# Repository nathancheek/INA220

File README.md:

# INA220
Lightweight Arduino library for the `INA220` / `INA220-Q1` / `INA219` current sensor

## Introduction
This library is based off [`SV-Zanshin/INA`](https://github.com/SV-Zanshin/INA) but is rearchitected to be much more lightweight.

Each instance of this library class configures all devices with the same settings, and unlike [`SV-Zanshin/INA`](https://github.com/SV-Zanshin/INA) it doesn't rely on EEPROM to store this information. If you need to configure some sensors differently, create a new instance of this class for each unique configuration.

## Breakout Board
An example breakout board is available under [`breakout-pcb`](breakout-pcb). EAGLE files are included, along with Gerber files and a schematic PDF. The Gerber .zip file includes a Bill of Materials and SMD Pick and Place files.

The board can be manufactured by uploading the Gerber .zip file to OSH Park, JLCPCB, or another PCB fabrication website.

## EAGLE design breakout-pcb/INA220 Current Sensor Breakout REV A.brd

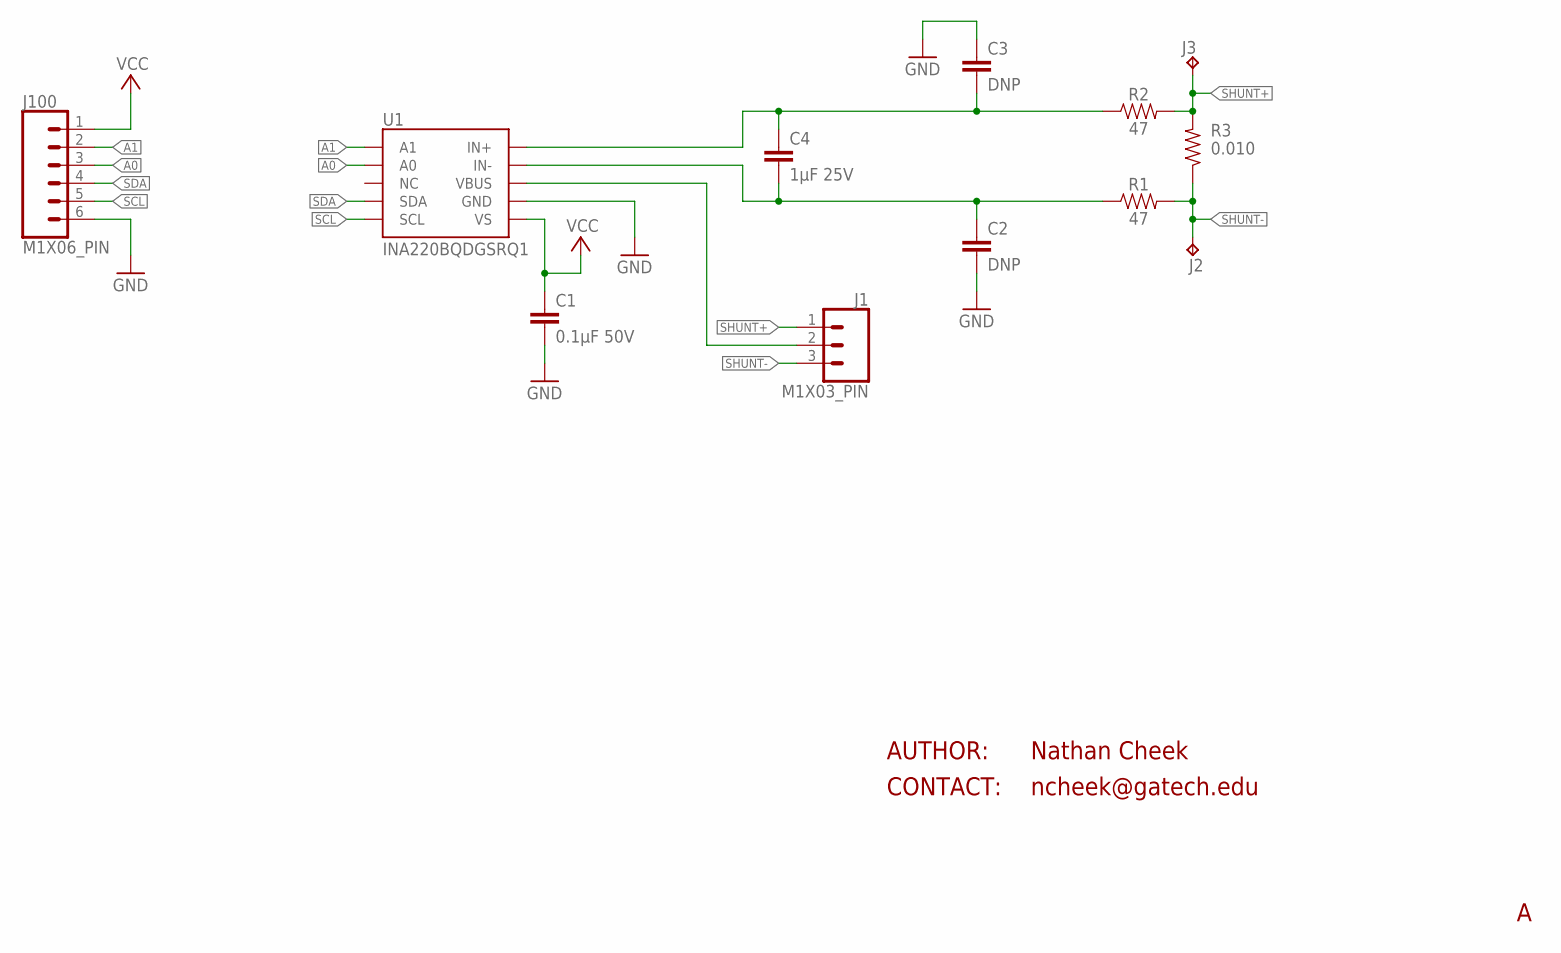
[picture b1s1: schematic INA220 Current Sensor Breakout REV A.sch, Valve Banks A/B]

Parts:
C1: 0.1µF 50V; C0603
C2, C3: DNP; C0603
C4: 1µF 25V; C0603
J1: M1X03_PIN; 1X03
J2, J3: BANANA_KEYSTONE_575-4; 575
J100: M1X06_PIN; 1X06
R1, R2: 47; R0603
R3: 0.010; R0805
U1: INA220BQDGSRQ1; VSSOP-10

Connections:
A0: J100.3, U1.P$2 (A0)
A1: J100.2, U1.P$1 (A1)
GND: C1.2, C2.1, C3.2, J100.6, U1.P$7 (GND)
unnamed: J1.2, U1.P$8 (VBUS)
unnamed: C2.2, C4.1, R1.1, U1.P$9 (IN-)
unnamed: C3.1, C4.2, R2.1, U1.P$10 (IN+)
SCL: J100.5, U1.P$5 (SCL)
SDA: J100.4, U1.P$4 (SDA)
SHUNT+: J1.1, J3.P$1, R2.2, R3.2
SHUNT-: J1.3, J2.P$1, R1.2, R3.1
VCC: C1.1, J100.1, U1.P$6 (VS)

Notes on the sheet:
AUTHOR:
CONTACT:

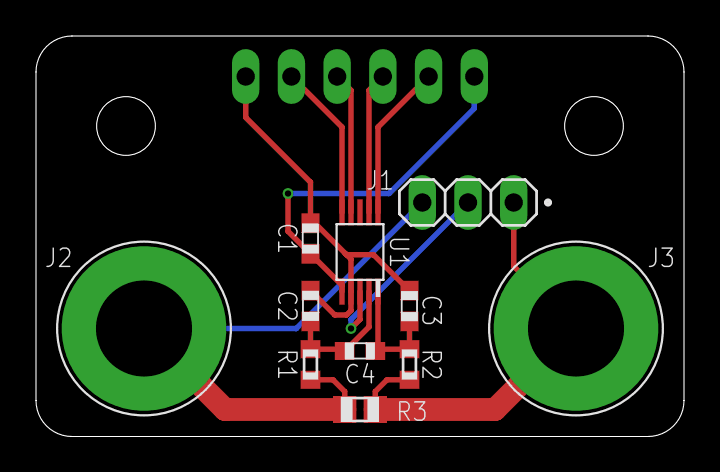
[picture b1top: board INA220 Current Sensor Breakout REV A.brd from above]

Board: 2 copper layers, 36.0 x 22.2 mm, 12 parts (1 on the bottom side), 11 nets.

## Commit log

2020-07-03 Add initial library files
2020-07-03 Add example, library properties
2020-07-03 Add keywords
2020-07-04 Function documentation update
2021-10-22 Add Breakout Board
2022-03-24 Changed to use Wire1 I2C port. Added check for overflow on constructor Added CCHM Example program
2022-03-29 Added Wire reference passing to the begin() of the library to support dual I2C ports Tested with Teensy 4.1. Added check to see if there is overflow in the calculation for the CAL register. It was si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
2022-03-29 Removed CCHM_Test example, and assert.h from INA220.h
2022-04-07 Removed Spurious include
2023-12-31 Fix ADC mode bug, clean up masks
2023-12-31 Clean up binary literal
2023-12-31 Documentation, comments
